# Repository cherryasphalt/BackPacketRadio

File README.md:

# BackPacketRadio
Hooking up portable radios with bluetooth interfaces for data packet transmission.

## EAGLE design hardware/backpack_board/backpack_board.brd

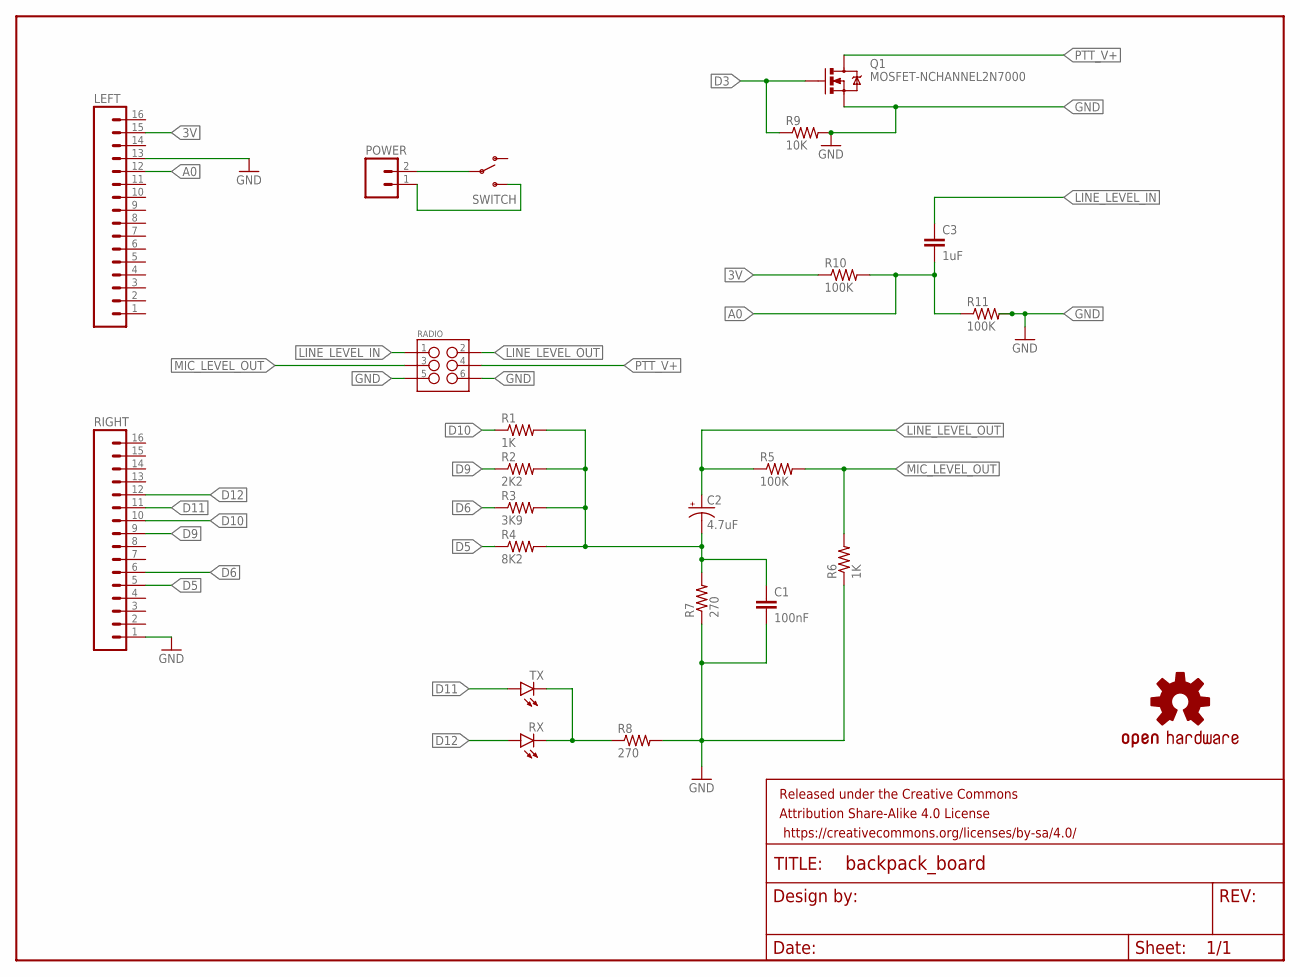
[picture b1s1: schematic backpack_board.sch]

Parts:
C1: 100nF; CAP-PTH-SMALL
C2: 4.7uF; CPOL-RADIAL-10UF-25V
C3: 1uF; CAP-PTH-SMALL
FRAME1: FRAME-LETTERNO_PACKAGE; DUMMY
LEFT: M16PTH; 1X16
LOGO1: OSHW-LOGOM; OSHW-LOGO-M
POWER: M02PTH; 1X02
Q1: MOSFET-NCHANNEL2N7000; TO-92
R1, R6: 1K; AXIAL-0.4
R2: 2K2; AXIAL-0.4
R3: 3K9; AXIAL-0.4
R4: 8K2; AXIAL-0.4
R5, R10, R11: 100K; AXIAL-0.4
R7, R8: 270; AXIAL-0.4
R9: 10K; AXIAL-0.4
RADIO: M03X2FEMALE; 2X3
RIGHT: M16PTH; 1X16
RX: LED3MM
SWITCH: SWITCH-SPDTPTH; SWITCH-SPDT
TX: LED3MM

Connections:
3V: LEFT.15, R10.P$1 (1)
A0: C3.2, LEFT.12, R10.P$2 (2), R11.P$1 (1)
D3: Q1.2 (G), R9.P$1 (1)
D5: R4.P$1 (1), RIGHT.5
D6: R3.P$1 (1), RIGHT.6
D9: R2.P$1 (1), RIGHT.9
D10: R1.P$1 (1), RIGHT.10
D11: RIGHT.11, TX.A
D12: RIGHT.12, RX.A
GND: C1.2, LEFT.13, Q1.1 (S), R6.P$1 (1), R7.P$1 (1), R8.P$2 (2), R9.P$2 (2), R11.P$2 (2), RADIO.5, RADIO.6, RIGHT.1
LINE_LEVEL_IN: C3.1, RADIO.1
LINE_LEVEL_OUT: C2.1 (+), R5.P$1 (1), RADIO.2
MIC_LEVEL_OUT: R5.P$2 (2), R6.P$2 (2), RADIO.3
unnamed: C1.1, C2.2 (-), R1.P$2 (2), R2.P$2 (2), R3.P$2 (2), R4.P$2 (2), R7.P$2 (2)
unnamed: POWER.2, SWITCH.2
unnamed: R8.P$1 (1), RX.K (C), TX.K (C)
PTT_V+: Q1.3 (D), RADIO.4
SWITCH: POWER.1, SWITCH.3 (S)

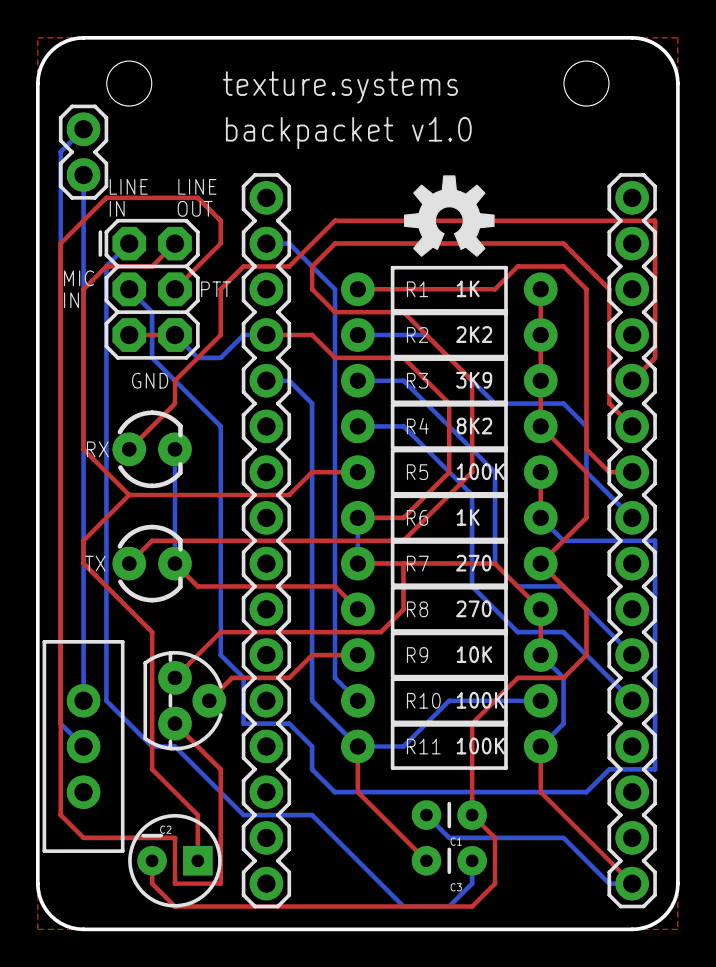
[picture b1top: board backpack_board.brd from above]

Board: 2 copper layers, 35.6 x 49.5 mm, 24 parts (0 on the bottom side), 18 nets.

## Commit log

2015-11-22 update gitignore
2015-11-22 board designs
2015-11-23 add silkscreen and drill holes to design
2015-11-23 add power switch
2015-11-28 arduino software
2015-12-22 start android app, start arduino

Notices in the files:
parts and their libraries:
SparkFun-Capacitors: Licensing: Creative Commons ShareAlike 4.0 International - https://creativecommons.org/licenses/by-sa/4.0
SparkFun-Aesthetics: Released under the Creative Commons Attribution Share-Alike 4.0 License
SparkFun-Aesthetics: https://creativecommons.org/licenses/by-sa/4.0
